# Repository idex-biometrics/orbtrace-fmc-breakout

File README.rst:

###########################
Orbtrace FMC Breakout Board
###########################

This FMC based breakout board is designed to interface an
`ORBTrace mini <https://orbcode.org/orbtrace-mini/>`_ to an Avnet
`Mini-ITX <https://www.avnet.com/wps/portal/us/products/avnet-boards/avnet-board-families/mini-itx/>`_
Zynq-7000 development board.

The board utilises the `Hirose DF40 <https://www.hirose.com/product/series/DF40>`_
series of board-to-board connectors.  This range is available in differing pin counts
and different stack heights.  However, many of the heights were unobtanium when putting
together the prototypes so your mileage may vary.  The part number used was the
`DF40C-(2.0)-70DS-0.4V <https://www.hirose.com/en/product/p/CL0684-4016-5-51>`_ which
is a 2mm mated stacking height.

****************
Revision History
****************

+--------+-------------------------------------------------------------------------------------+
| Tag    | Description                                                                         |
+========+=====================================================================================+
| 0.2.0  | Fixed orientation of FMC connector. Originally put down 180 degrees out after       |
|        | reviewing dimensions of a board that was viewed mirrored. D'oh.                     |
|        | Also added a legacy 20-pin IDC conector for JLink support and some 0.1" pin headers |
|        | for debug access when the ORBTrace is not mounted.                                  |
+--------+-------------------------------------------------------------------------------------+
| 0.1.0  | Initial commit.                                                                     |
+--------+-------------------------------------------------------------------------------------+

****************
Board Dimensions
****************

The board outline conforms to the ANSI/VITA 57.1 standard and I followed the mechanical
data section of the product pages for the
`FMCHUB LPC Breakout <https://fmchub.github.io/projects/FMC_LPC_BREAKOUT/Datasheet/FMC_LPC_BREAKOUT_datasheet.html>`_.

The mounting location of the FMC connector itself doesn't seem to be easily available
unless you pay for the specification. However, a few useful dimensions found on the net
and some scribbling on paper enabled the relative locations to the mounting holes to be
calculated.

This forum post for the
`Nexys4 DDR <https://forum.digilent.com/topic/1402-nexys4-ddr-mechanicals/?do=findComment&comment=9315>`_
shows the relative offsets.

**Note:** The ``User.Drawings`` layer of the PCB Editor has the exterior dimensions annotated.

**********
FMC Pinout
**********

The following tables show the pin assignments for each of the connectors on the board.

ORBTrace Mini
=============

The ORBTrace uses a high density 70 pin connector that is unused by default and is
available for user expansion purposes.  The use case for this breakout board is to
re-route the SWD interface from the 0.1" headers to use the high density connector.
Enough pins are available for further functionality to be implemented too.

+------+---------+-----------+---------+-----------------------------------------+
|  Pin | Signal  | Net       | FMC Pin | Function                                |
+======+=========+===========+=========+=========================================+
|  08  | LED_EXT |  N/A      | N/A     | RGB LED drive from Orbtrace; unused.    |
+------+---------+-----------+---------+-----------------------------------------+
|  09  | JTMS    | LA24_N    | H29     | FPGA JTAG lines.                        |
+------+---------+-----------+---------+-----------------------------------------+
|  11  | JTCK    | LA24_P    | H28     | FPGA JTAG lines.                        |
+------+---------+-----------+---------+-----------------------------------------+
|  13  | JTDI    | LA25_N    | G28     | FPGA JTAG lines.                        |
+------+---------+-----------+---------+-----------------------------------------+
|  15  | JTDO    | LA25_P    | G27     | FPGA JTAG lines.                        |
+------+---------+-----------+---------+-----------------------------------------+
|  14  | SDA     | LA28_N    | H32     | I2C from Orbtrace; unused.              |
+------+---------+-----------+---------+-----------------------------------------+
|  16  | SCL     | LA28_P    | H31     | I2C from Orbtrace; unused.              |
+------+---------+-----------+---------+-----------------------------------------+
|  22  | EXT_31  | LA29_P    | G30     | User IO free to use.                    |
+------+---------+-----------+---------+-----------------------------------------+
|  20  | EXT_30  | LA29_N    | G31     | User IO free to use.                    |
+------+---------+-----------+---------+-----------------------------------------+
|  28  | EXT_29  | TP2       | N/A     | User IO free to use.                    |
+------+---------+-----------+---------+-----------------------------------------+
|  26  | EXT_28  | TP1       | N/A     | User IO free to use.                    |
+------+---------+-----------+---------+-----------------------------------------+
|  25  | EXT_27  | LA22_N    | G25     | User IO free to use.                    |
+------+---------+-----------+---------+-----------------------------------------+
|  27  | EXT_26  | LA22_P    | G24     | User IO free to use.                    |
+------+---------+-----------+---------+-----------------------------------------+
|  32  | EXT_25  | TP3       | N/A     | User IO free to use.                    |
+------+---------+-----------+---------+-----------------------------------------+
|  34  | EXT_24  | TP4       | N/A     | User IO free to use.                    |
+------+---------+-----------+---------+-----------------------------------------+
|  19  | EXT_23  | LA21_N    | H26     | User IO free to use.                    |
+------+---------+-----------+---------+-----------------------------------------+
|  21  | EXT_22  | LA21_P    | H25     | User IO free to use.                    |
+------+---------+-----------+---------+-----------------------------------------+
|  31  | EXT_21  | LA19_N    | H23     | User IO free to use.                    |
+------+---------+-----------+---------+-----------------------------------------+
|  33  | EXT_20  | LA19_P    | H22     | User IO free to use.                    |
+------+---------+-----------+---------+-----------------------------------------+
|  39  | EXT_19  | LA20_P    | G21     | User IO free to use.                    |
+------+---------+-----------+---------+-----------------------------------------+
|  37  | EXT_18  | LA20_N    | G22     | User IO free to use.                    |
+------+---------+-----------+---------+-----------------------------------------+
|  38  | EXT_17  | LA07_N    | H14     | User IO free to use.                    |
+------+---------+-----------+---------+-----------------------------------------+
|  40  | EXT_16  | LA07_P    | H13     | User IO free to use.                    |
+------+---------+-----------+---------+-----------------------------------------+
|  46  | EXT_15  | LA04_P    | H10     | User IO free to use.                    |
+------+---------+-----------+---------+-----------------------------------------+
|  44  | EXT_14  | LA04_N    | H11     | User IO free to use.                    |
+------+---------+-----------+---------+-----------------------------------------+
|  43  | EXT_13  | LA15_N    | H20     | User IO free to use.                    |
+------+---------+-----------+---------+-----------------------------------------+
|  45  | EXT_12  | LA15_P    | H19     | User IO free to use.                    |
+------+---------+-----------+---------+-----------------------------------------+
|  57  | EXT_11  | LA11_P    | H16     | User IO free to use.                    |
+------+---------+-----------+---------+-----------------------------------------+
|  55  | EXT_10  | LA11_N    | H17     | User IO free to use.                    |
+------+---------+-----------+---------+-----------------------------------------+
|  50  | EXT_09  | LA03_N    | G10     | User IO free to use.                    |
+------+---------+-----------+---------+-----------------------------------------+
|  52  | EXT_08  | LA03_P    | G9      | User IO free to use.                    |
+------+---------+-----------+---------+-----------------------------------------+
|  49  | EXT_07  | LA16_N    | G19     | User IO free to use.                    |
+------+---------+-----------+---------+-----------------------------------------+
|  51  | EXT_06  | LA16_P    | G18     | User IO free to use.                    |
+------+---------+-----------+---------+-----------------------------------------+
|  58  | EXT_05  | LA00_P_CC | G6      | User IO free to use. Clock capable.     |
+------+---------+-----------+---------+-----------------------------------------+
|  56  | EXT_04  | LA00_N_CC | G7      | User IO free to use. Clock capable.     |
+------+---------+-----------+---------+-----------------------------------------+
|  61  | EXT_03  | CFG1      | N/A     | User config; driven from DIP switch.    |
+------+---------+-----------+---------+-----------------------------------------+
|  63  | EXT_02  | CFG2      | N/A     | User config; driven from DIP switch.    |
+------+---------+-----------+---------+-----------------------------------------+
|  64  | EXT_01  | PB2       | N/A     | User push button.                       |
+------+---------+-----------+---------+-----------------------------------------+
|  62  | EXT_00  | PB4       | N/A     | User push button.                       |
+------+---------+-----------+---------+-----------------------------------------+

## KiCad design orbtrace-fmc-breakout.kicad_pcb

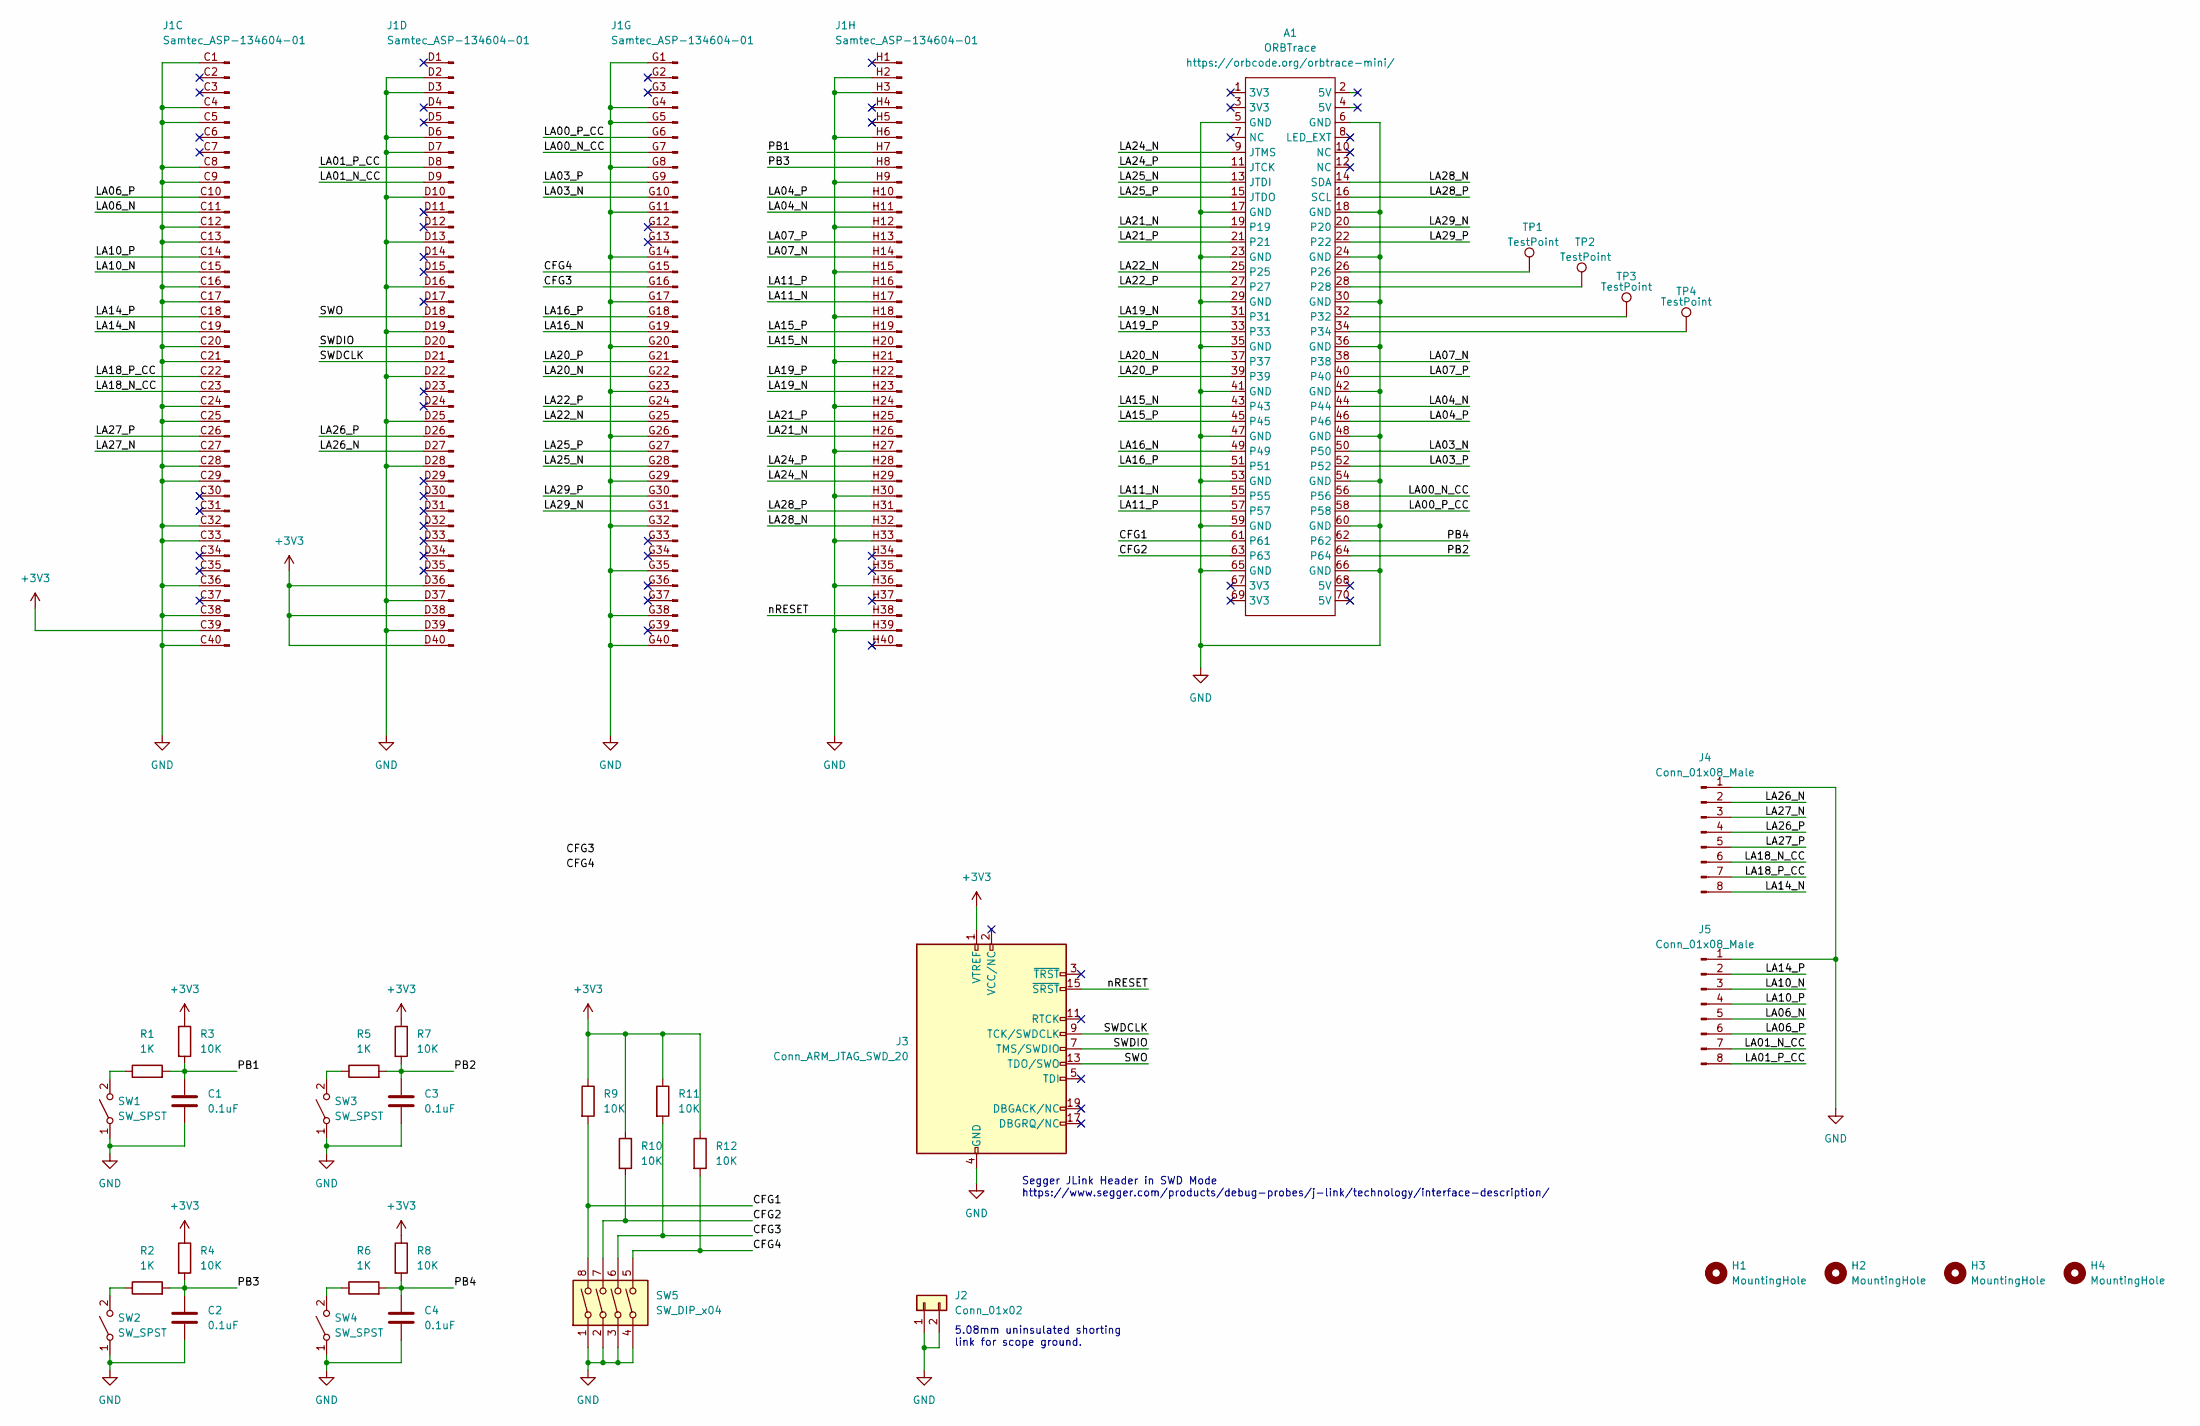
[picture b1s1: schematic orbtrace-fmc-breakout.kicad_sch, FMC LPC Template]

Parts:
A1: ORBTrace
C1, C2, C3, C4: 0.1uF; C_0603_1608Metric
H1, H2, H3, H4: MountingHole; MountingHole_2.7mm_M2.5_ISO14580
J1: Samtec_ASP-134604-01; Samtec_FMC_ASP-134604-01_4x40_Vertical_Renamed
J2: Conn_01x02; Shorting_Link_5.08mm
J3: Conn_ARM_JTAG_SWD_20; IDC-Header_2x10_P2.54mm_Vertical
J4, J5: Conn_01x08_Male; PinHeader_1x08_P2.54mm_Vertical
R1, R2, R5, R6: 1K; R_0603_1608Metric
R3, R4, R7, R8, R9, R10, R11, R12: 10K; R_0603_1608Metric
SW1, SW2, SW3, SW4: SW_SPST; SW_Push_1P1T_NO_Vertical_Wuerth_434133025816
SW5: SW_DIP_x04; SW_DIP_SPSTx04_Slide_Omron_A6S-410x_W8.9mm_P2.54mm
TP1, TP2, TP3, TP4: TestPoint; TestPoint_Harwin_S2761-46R

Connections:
+3V3: J1.C39 (Pin_39), J1.D36 (Pin_36), J1.D38 (Pin_38), J1.D40 (Pin_40), J3.1 (VTREF), R3.1, R4.1, R7.1, R8.1, R9.1, R10.1, R11.1, R12.1
/CFG1: A1.61, R9.2, SW5.8
/CFG2: A1.63, R10.2, SW5.7
/CFG3: J1.G16 (Pin_16), R11.2, SW5.6
/CFG4: J1.G15 (Pin_15), R12.2, SW5.5
/LA00_N_CC: A1.56, J1.G7 (Pin_7)
/LA00_P_CC: A1.58, J1.G6 (Pin_6)
/LA01_N_CC: J1.D9 (Pin_9), J5.7
/LA01_P_CC: J1.D8 (Pin_8), J5.8
/LA03_N: A1.50, J1.G10 (Pin_10)
/LA03_P: A1.52, J1.G9 (Pin_9)
/LA04_N: A1.44, J1.H11 (Pin_11)
/LA04_P: A1.46, J1.H10 (Pin_10)
/LA06_N: J1.C11 (Pin_11), J5.5
/LA06_P: J1.C10 (Pin_10), J5.6
/LA07_N: A1.38, J1.H14 (Pin_14)
/LA07_P: A1.40, J1.H13 (Pin_13)
/LA10_N: J1.C15 (Pin_15), J5.3
/LA10_P: J1.C14 (Pin_14), J5.4
/LA11_N: A1.55, J1.H17 (Pin_17)
/LA11_P: A1.57, J1.H16 (Pin_16)
/LA14_N: J1.C19 (Pin_19), J4.8
/LA14_P: J1.C18 (Pin_18), J5.2
/LA15_N: A1.43, J1.H20 (Pin_20)
/LA15_P: A1.45, J1.H19 (Pin_19)
/LA16_N: A1.49, J1.G19 (Pin_19)
/LA16_P: A1.51, J1.G18 (Pin_18)
/LA18_N_CC: J1.C23 (Pin_23), J4.6
/LA18_P_CC: J1.C22 (Pin_22), J4.7
/LA19_N: A1.31, J1.H23 (Pin_23)
/LA19_P: A1.33, J1.H22 (Pin_22)
/LA20_N: A1.37, J1.G22 (Pin_22)
/LA20_P: A1.39, J1.G21 (Pin_21)
/LA21_N: A1.19, J1.H26 (Pin_26)
/LA21_P: A1.21, J1.H25 (Pin_25)
/LA22_N: A1.25, J1.G25 (Pin_25)
/LA22_P: A1.27, J1.G24 (Pin_24)
/LA24_N: A1.9 (JTMS), J1.H29 (Pin_29)
/LA24_P: A1.11 (JTCK), J1.H28 (Pin_28)
/LA25_N: A1.13 (JTDI), J1.G28 (Pin_28)
/LA25_P: A1.15 (JTDO), J1.G27 (Pin_27)
/LA26_N: J1.D27 (Pin_27), J4.2
/LA26_P: J1.D26 (Pin_26), J4.4
/LA27_N: J1.C27 (Pin_27), J4.3
/LA27_P: J1.C26 (Pin_26), J4.5
/LA28_N: A1.14 (SDA), J1.H32 (Pin_32)
/LA28_P: A1.16 (SCL), J1.H31 (Pin_31)
/LA29_N: A1.20, J1.G31 (Pin_31)
/LA29_P: A1.22, J1.G30 (Pin_30)
/PB1: C1.1, J1.H7 (Pin_7), R1.2, R3.2
/PB2: A1.64, C3.1, R5.2, R7.2
/PB3: C2.1, J1.H8 (Pin_8), R2.2, R4.2
/PB4: A1.62, C4.1, R6.2, R8.2
/SWDCLK: J1.D21 (Pin_21), J3.9 (TCK/SWDCLK)
/SWDIO: J1.D20 (Pin_20), J3.7 (TMS/SWDIO)
/SWO: J1.D18 (Pin_18), J3.13 (TDO/SWO)
/nRESET: J1.H38 (Pin_38), J3.15 (~SRST)
GND: A1.5 (GND), A1.6 (GND), A1.17 (GND), A1.18 (GND), A1.23 (GND), A1.24 (GND), A1.29 (GND), A1.30 (GND), A1.35 (GND), A1.36 (GND), A1.41 (GND), A1.42 (GND), A1.47 (GND), A1.48 (GND), A1.53 (GND), A1.54 (GND), A1.59 (GND), A1.60 (GND), A1.65 (GND), A1.66 (GND), C1.2, C2.2, C3.2, C4.2, J1.C1 (Pin_1), J1.C4 (Pin_4), J1.C5 (Pin_5), J1.C8 (Pin_8), J1.C9 (Pin_9), J1.C12 (Pin_12), J1.C13 (Pin_13), J1.C16 (Pin_16), J1.C17 (Pin_17), J1.C20 (Pin_20), J1.C21 (Pin_21), J1.C24 (Pin_24), J1.C25 (Pin_25), J1.C28 (Pin_28), J1.C29 (Pin_29), J1.C32 (Pin_32), J1.C33 (Pin_33), J1.C36 (Pin_36), J1.C38 (Pin_38), J1.C40 (Pin_40), J1.D2 (Pin_2), J1.D3 (Pin_3), J1.D6 (Pin_6), J1.D7 (Pin_7), J1.D10 (Pin_10), J1.D13 (Pin_13), J1.D16 (Pin_16), J1.D19 (Pin_19), J1.D22 (Pin_22), J1.D25 (Pin_25), J1.D28 (Pin_28), J1.D37 (Pin_37), J1.D39 (Pin_39), J1.G1 (Pin_1), J1.G4 (Pin_4), J1.G5 (Pin_5), J1.G8 (Pin_8), J1.G11 (Pin_11), J1.G14 (Pin_14), J1.G17 (Pin_17), J1.G20 (Pin_20), J1.G23 (Pin_23), J1.G26 (Pin_26), J1.G29 (Pin_29), J1.G32 (Pin_32), J1.G35 (Pin_35), J1.G38 (Pin_38), J1.G40 (Pin_40), J1.H2 (Pin_2), J1.H3 (Pin_3), J1.H6 (Pin_6), J1.H9 (Pin_9), J1.H12 (Pin_12), J1.H15 (Pin_15), J1.H18 (Pin_18), J1.H21 (Pin_21), J1.H24 (Pin_24), J1.H27 (Pin_27), J1.H30 (Pin_30), J1.H33 (Pin_33), J1.H36 (Pin_36), J1.H39 (Pin_39), J2.1, J2.2, J3.4 (GND), J3.6 (GND), J3.8 (GND), J3.10 (GND), J3.12 (GND), J3.14 (GND), J3.16 (GND), J3.18 (GND), J3.20 (GND), J4.1, J5.1, SW1.1 (A), SW2.1 (A), SW3.1 (A), SW4.1 (A), SW5.1, SW5.2, SW5.3, SW5.4
unnamed: A1.26, TP1.1
unnamed: A1.28, TP2.1
unnamed: A1.32, TP3.1
unnamed: A1.34, TP4.1
unnamed: R1.1, SW1.2 (B)
unnamed: R2.1, SW2.2 (B)
unnamed: R5.1, SW3.2 (B)
unnamed: R6.1, SW4.2 (B)

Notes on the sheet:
Segger JLink Header in SWD Mode https://www.segger.com/products/debug-probes/j-link/technology/interface-description/
5.08mm uninsulated shorting link for scope ground.

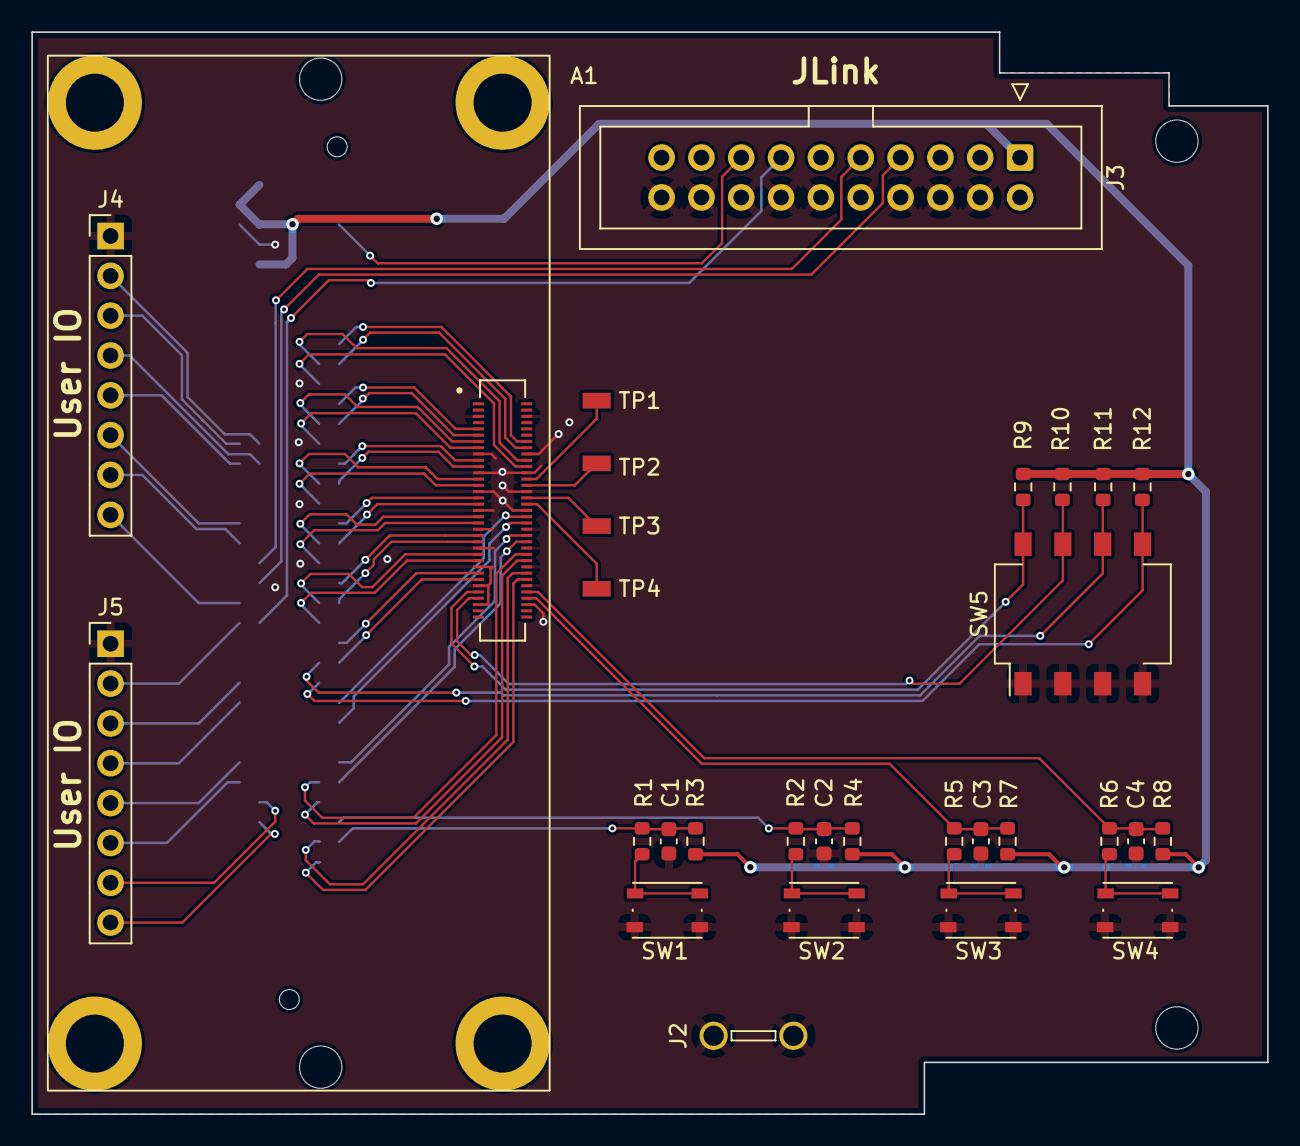
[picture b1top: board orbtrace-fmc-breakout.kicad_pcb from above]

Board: 2 copper layers, 78.8 x 69.0 mm, 35 parts (1 on the bottom side), 66 nets.

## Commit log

2022-08-24 First commit.
    Adding first pass at the ORBTrace breakout for the Avnet mini-itx board.
2022-08-24 Adding pinout spreadsheet
2023-08-04 dev: fix for misaligned FMC
    This commit fixes the FMC orientation by rotating it 180 degrees. The
    original layout was created while looking at a mirrored view of an
    example FMC expansion board - oops.
    This update also adds a standard 20-pin 0.1" pitch Arm debug connector
    that is wired for SWD only. In addition there are 2 8-pin 0.1" headers
    connected to FPGA IO that can be used for user IO of any sort.
2023-08-04 dev: update to KiCAD v7
2023-08-04 dev: Adding README and directory tidyup
